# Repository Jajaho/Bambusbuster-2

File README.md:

# Bambusbuster-2
Electronic minimum quantity lubrication system.

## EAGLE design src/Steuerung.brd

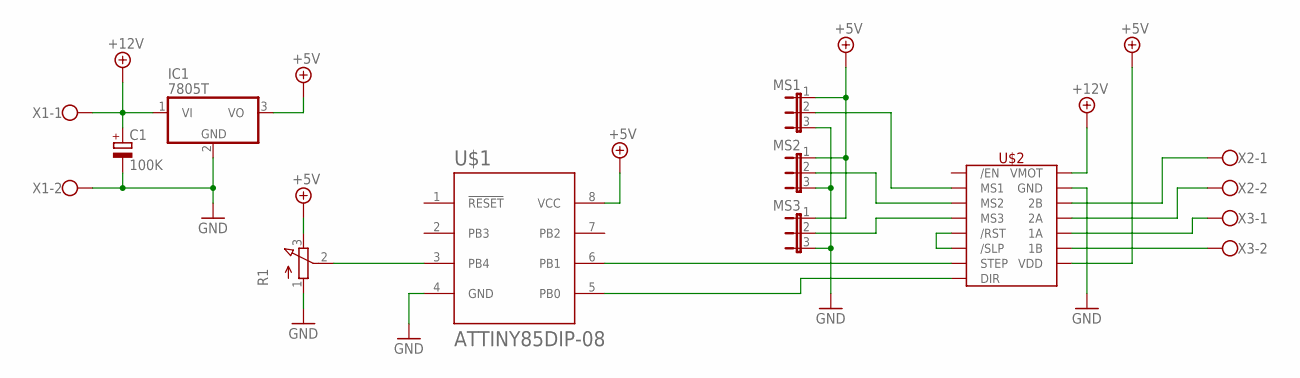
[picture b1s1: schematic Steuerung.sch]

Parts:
C1: 100K; E2-5
IC1: 7805T; TO220H
MS1, MS2, MS3: JP2E; JP2
R1: 3RP/1610N
U$1: ATTINY85DIP-08; DIP900W57P254L920H431Q8B
U$2: A4988_STEP
X1, X2, X3: W237-102

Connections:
+5V: IC1.3 (VO), MS1.1, MS2.1, MS3.1, R1.3 (E), U$1.8 (VCC), U$2.VDD
+12V: C1.+, IC1.1 (VI), U$2.VMOT, X1.1
GND: C1.-, IC1.2 (GND), MS1.3, MS2.3, MS3.3, R1.1 (A), U$1.4 (GND), U$2.GND, U$2.GND2 (GND), X1.2
unnamed: U$2.2B, X2.1
unnamed: U$2.2A, X2.2
unnamed: U$2.1A, X3.1
unnamed: U$2.1B, X3.2
unnamed: R1.2 (S), U$1.3 (PB4)
unnamed: U$1.5 (PB0), U$2.DIR
unnamed: U$1.6 (PB1), U$2.STEP
unnamed: MS3.2, U$2.MS3
unnamed: MS2.2, U$2.MS2
unnamed: MS1.2, U$2.MS1
unnamed: U$2./RST, U$2./SLP

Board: 2 copper layers, 11 parts (0 on the bottom side), 14 nets, no tracks yet.

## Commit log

2023-07-06 Add eagle project files
